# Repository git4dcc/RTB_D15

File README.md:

# RTB_D15

My Homebrew [D15](https://rtb4dcc.de/hardware/decoder/d15/) decoder is a drop in replacement for the original analog Minitrix (#11130) PCB. The decoder is designed to integrate into the [RTB](https://rtb4dcc.de/concept/) digital control infrastructure.

<details>
<summary>See also</summary>

- [RTB_D12 - custom](/../../../../git4dcc/RTB_D12) (Fleischmann V100)
- [RTB_D13 - custom](/../../../../git4dcc/RTB_D13) (Minitrix coach)
- [RTB_D16 - NEM651](/../../../../git4dcc/RTB_D16)
- [RTB_D20 - NEM651](/../../../../git4dcc/RTB_D20)
- [RTB_D21 - Next18](/../../../../git4dcc/RTB_D21)
- [RTB_D22 - Plux16](/../../../../git4dcc/RTB_D22)
- [RTB_D23 - NEM652](/../../../../git4dcc/RTB_D23)

</details>

<details>
<summary>User Guides</summary>

- User Guide - DE
- [User Guide - EN](https://rtb4dcc.de/rtb_decoder_reference_en/)

</details>

<br>

## Decoder features
- **Minitirx V160** PCB decoder
- **DCC**
  - DCC-A automatic logon
  - DCC-R protocol extension
  - Service Mode Programming
- **Railcom**
  - Channel 1/2
  - POM, xPOM
  - DYN: Speed, QoS, Track-voltage, Motor-current, AUX-current, Temp, Distance travelled
- 7-18V track voltage
- heartbeat LED
- adjustable max motor current (default 250mA)
- adjustable max AUX current (default 250mA)
- over temp protection
- Function output: LF/LR (dimmable, 1.4kHz), LED on PCB
- Function output: AUX1/AUX2 (dimmable, 1.4kHz) for driver cabin (LEDs on PCB)
- Function output: AUX3/AUX4 logic level
- Function output: AUX5/AUX6 open drain (each 250mA)
- buffer capacitor 4x330uF
- optional 9-axis orientation sensor
- <10mA idle power consumption
- Firmware update over main tracks via DCC-R protocol

# Hardware
The current PCB layout uses SMD footprints with 0.5mm pitch and mainly 0402 parts. Reflow soldering is mandatory whereas handsoldering almost impossible.

## PCB
- 4-layer PCB, FR4, 0.8mm
- CPU: AVR64DA32
- Motor bridge: DRV8231
- Inrush limiter: TPS22810
- 9-axis absolute-orientation sensor: BNO055

## Kicad
[Schematic](doc/D12_schematic.pdf) | [Layout](doc/D12_layout.pdf) | [Gerber](gerber)

<details>
<summary>Dependency</summary>
<br>

:yellow_circle: Requires my Kicad project library [RTB_SamacSys](https://github.com/git4dcc/RTB_SamacSys) in the same directory tree.

</details>

## Firmware
Filename structure: { **pcb** }{ **code** }{ **version** }.hex

Example: **D15F0001**.hex

|   | Description |
| --- | --- |
| **pcb** | Name of matching hardware (**D12**) |
| **code** | Type of code contained (**R**=rom, **B**=bootloader, **F**=flash, **U**=bld update, **P**=UPDI factory code) |
| **version** | Release version (**####**) |

[Firmware files](firmware)

# Images

# YouTube
See the D15 decoder (rev 0) in action.<br><br>

This project is intended for hobby use only and is distributed in accordance with the Apache License 2.0 agreement.

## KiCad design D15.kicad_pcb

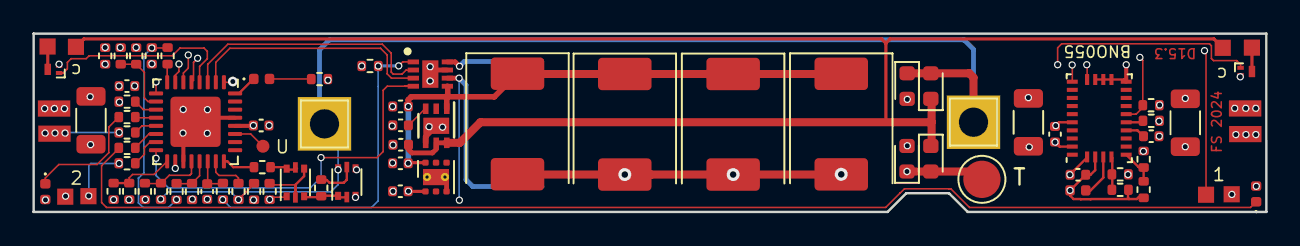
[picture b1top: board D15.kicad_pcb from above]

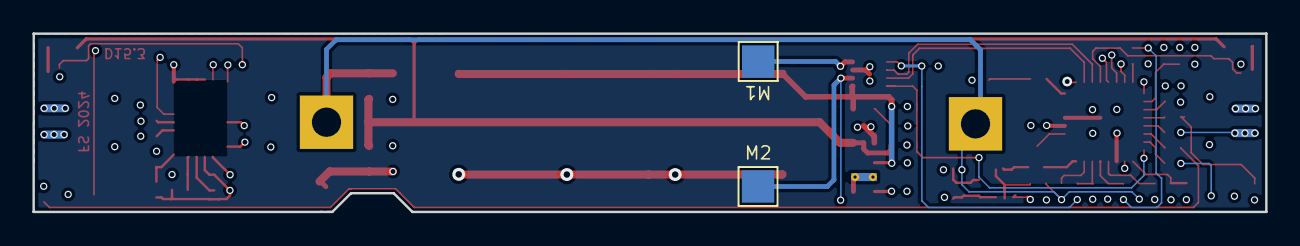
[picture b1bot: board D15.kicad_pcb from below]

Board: 4 copper layers, 76.0 x 11.0 mm, 83 parts (2 on the bottom side), 52 nets.

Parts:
C1, C5, C11: 100n/50V; C_0402_1005Metric
C2, C6, C8, C9, C10, C13: 100n; C_0402_1005Metric
C3, C7, C17, C18: 330u/25V; CP_EIA-7361-38_AVX-V
C4, C14, C15: 220u/6V; C_1206_3216Metric
C12: 4.7u/6V; C_0402_1005Metric
C22: 1u/25V; C_0402_1005Metric
D1, D5: white; LED_0402_1005Metric
D2, D4, D7, D8: CDBURT0530; D_0603_1608Metric
D3: LED_Small; LED_0402_1005Metric
H1: MountingHole_Pad; TestPoint_THTPad_2.5x2.5mm_Drill1.2mm
H2: MountingHole; TestPoint_THTPad_2.5x2.5mm_Drill1.2mm
IC1: DRV8231ADSGR; SON50P200X200X80-9N
IC2: NCP730BM; WSON-6-1EP_2x2mm_P0.65mm_EP1x1.6mm_ThermalVias
J1, J6, J7, J8, J9, J10, J11, J12, J13, J14, J15, J16, J17: Conn_01x01; DummyNet-Connector
J2, J3: Conn_01x01; TestPoint_THTPad_2.0x2.0mm_Drill1.0mm
J4: Conn_01x01; TestPoint_Pad_D2.5mm
Q1: BC857BDW1; SOT-666
Q2: BC847BDW1; SOT-666
Q3, Q4: PMZB200UNEYL; Diodes_DFN1006-3
R1, R4, R5, R6, R16, R26, R27: 3.3k; R_0402_1005Metric
R2, R7, R8, R10, R12: 33k; R_0402_1005Metric
R3: 22; R_0402_1005Metric
R9, R34, R35: 220k; R_0402_1005Metric
R11, R13: 12k; R_0402_1005Metric
R14, R15, R18, R19, R20, R21, R22, R23, R24, R25: 10k; R_0402_1005Metric
R17: 1k; R_0402_1005Metric
R36, R37: 9.1k; R_0402_1005Metric
U1: AVR-64DA32; VQFN-32-1EP_5x5mm_P0.5mm_EP3.1x3.1mm
U3: BNO055; LGA-28_5.2x3.8mm_P0.5mm
U4: TPS22810DRVR; DFN-6-1EP_2x2mm_P0.65mm_EP1x1.6mm

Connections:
+3V3: C4.1, C6.2, C9.2, C10.2, C12.1, C13.2, C14.1, C15.1, D1.2, D5.2, IC2.1, J10.1, J12.1, Q1.1, R3.1, R14.2, R23.2, R24.2, R25.2, R26.2, U1.18, U1.28, U3.3, U3.28
AUX.3: R27.1, U1.9
AUX.4: R16.1, U1.15
AUX.5: Q3.1, U1.4
AUX.6: Q4.1, U1.1
BNO.res: R2.2, U1.5, U3.11
BNO.rx: U1.7, U3.20
BNO.tx: U1.6, U3.19
DCC-a: D2.1, D4.2, J4.1, Q2.3, R7.1, R19.2, R34.1
DCC-b: D7.2, D8.1, H1.1, H2.1, Q2.6, R8.1, R20.2, R35.1
GND: C1.2, C2.2, C3.2, C4.2, C5.2, C6.1, C7.2, C8.1, C9.1, C10.1, C11.2, C12.2, C13.1, C14.2, C15.2, C17.2, C18.2, C22.2, D2.2, D8.2, IC1.7, IC1.9, IC2.3, IC2.7, J6.1, J7.1, Q2.4, Q3.2, Q4.2, R2.1, R11.1, R13.1, R17.1, R19.1, R20.1, R21.1, R22.1, R36.2, R37.2, U1.19, U1.29, U1.33, U3.2, U3.15, U3.16, U3.17, U3.18, U3.25, U4.4, U4.7
ISENS: C22.1, R9.2, U1.22
LED.F.cab: R5.1, U1.12
LED.F.wht: R1.1, U1.13
LED.R.cab: R6.1, U1.14
LED.R.wht: R4.1, U1.11
LED.hbt: D3.1, U1.32
M1: IC1.8, J2.1, R12.2
M2: IC1.6, J3.1, R10.2
unnamed: C2.1, U4.3
unnamed: C8.2, U3.9
unnamed: D1.1, R5.2
unnamed: D3.2, R26.1
unnamed: D5.1, R6.2
unnamed: IC1.1, R9.1, R17.2
unnamed: J1.1, R16.2
unnamed: J8.1, R27.2
unnamed: J9.1, R1.2
unnamed: J11.1, R4.2
unnamed: J13.1, Q3.3
unnamed: J14.1, Q4.3
unnamed: Q1.2, Q1.4, R3.2
unnamed: Q1.3, Q2.1, Q2.2, R18.2
unnamed: Q1.5, Q1.6, R15.2
unnamed: Q2.5, R18.1
unnamed: R7.2, U1.8
unnamed: R8.2, U1.23
unnamed: R14.1, U3.4
unnamed: R21.2, R24.1, U3.6
unnamed: R22.2, R23.1, U3.5
unnamed: R25.1, U3.10
PWM1: IC1.2, U1.3
PWM2: IC1.3, U1.2
RCM.tx: R15.1, U1.24
UDCC-a: R34.2, R36.1, U1.21
UDCC-b: R35.2, R37.1, U1.20
UPDI: J17.1, U1.27
VHBR: C1.1, C3.1, C7.1, C11.1, C17.1, C18.1, IC1.5, IC2.6, U4.1
VTRK: C5.1, D4.1, D7.1, J15.1, J16.1, U4.5, U4.6
Vref: IC1.4, U1.16
uSENS1: R12.1, R13.2, U1.10
uSENS2: R10.1, R11.2, U1.17

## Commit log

2024-09-29 Changed H-Bridge, added hardware PWM
2025-03-23 add: decoder lock
2025-08-05 mod: led automation
2026-02-20 git mirror test
